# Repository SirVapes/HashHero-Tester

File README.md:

# HashHero
 Open Source Antminer Hashboard Tester

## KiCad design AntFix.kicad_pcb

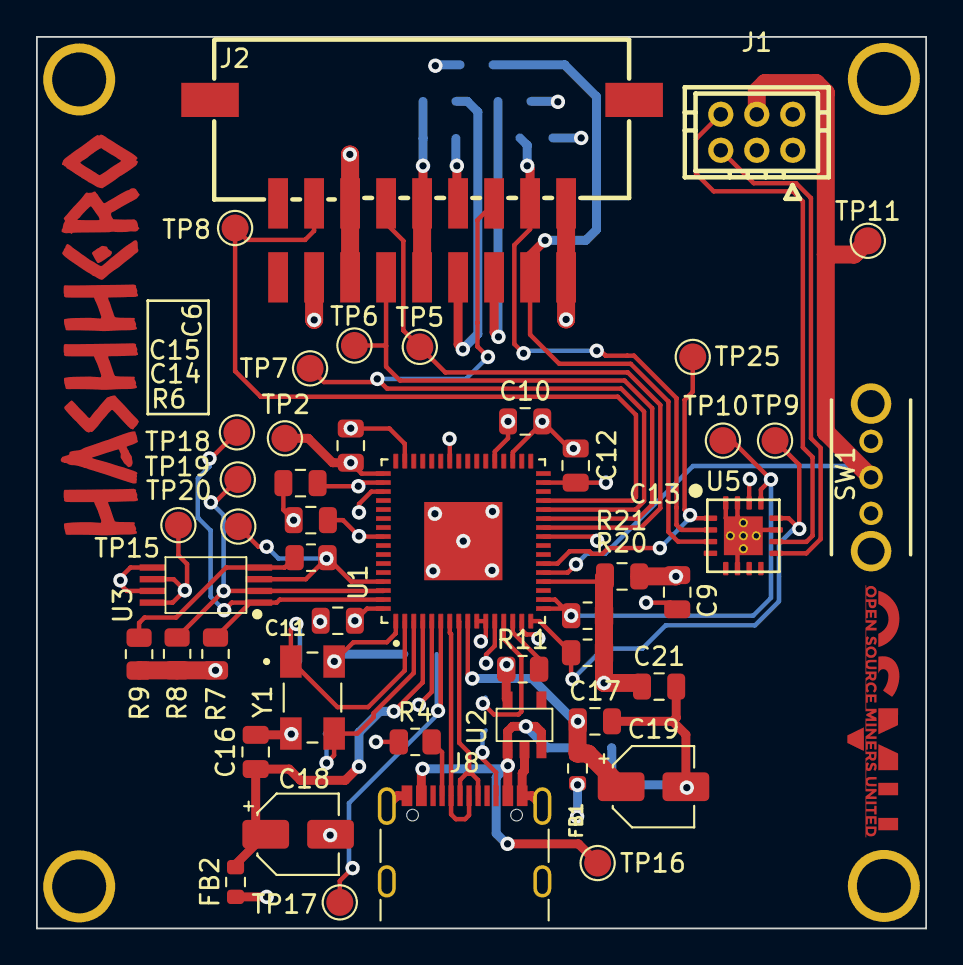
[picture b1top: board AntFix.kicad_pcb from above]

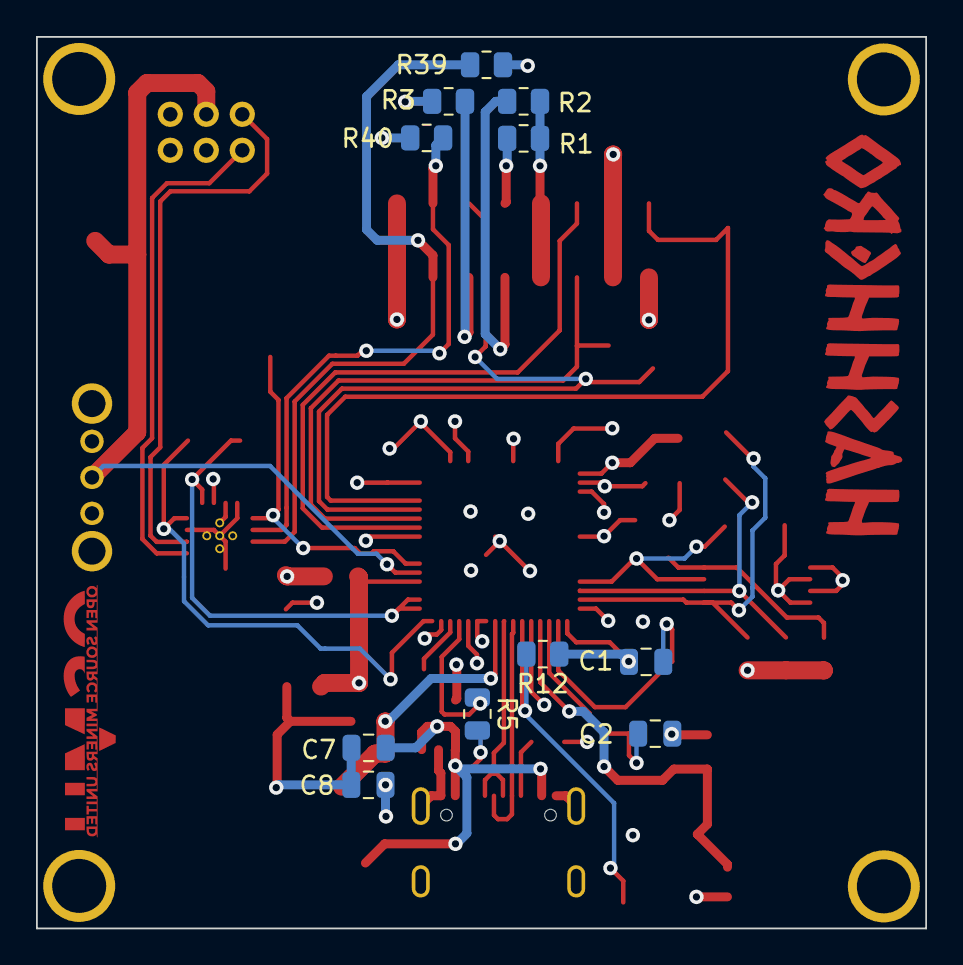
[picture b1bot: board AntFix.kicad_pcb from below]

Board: 4 copper layers, 49.4 x 49.5 mm, 62 parts (11 on the bottom side), 33 nets.

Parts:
C1, C2: 27pf; C_0805_2012Metric
C6: 3.3uF; C_0805_2012Metric
C7, C8: 1uF; C_0805_2012Metric
C9, C10, C11, C12, C13, C14, C15, C16, C17, C21: 0.1uF; C_0805_2012Metric
C18, C19: 4.7uF; CP_Elec_4x5.4
FB1, FB2: FerriteBead_Small; R_0603_1608Metric
H1, H2, H3, H4: MountingHole_Pad; MountingHole_3mm_Pad
J1: PSU Comm; CONN-TH_6P-P2.00_PHD-2X3A
J2: Hashboard0; CONN-SMD_X2026WRS-2X09D-LPSW
J8: USB_C_Receptacle_USB2.0; USB_C_Receptacle_GCT_USB4105-xx-A_16P_TopMnt_Horizontal
R1, R2, R3, R20, R21, R39, R40: 4.7K; R_0805_2012Metric
R4, R5: 5.1K; R_0805_2012Metric
R6: 2.2K; R_0805_2012Metric
R7, R8, R9: 10K; R_0805_2012Metric
R11: 1K; R_0805_2012Metric
R12: 12K; R_0805_2012Metric
SW1: SW_SPDT; OS102011MA1QN1
TP2, TP5, TP6, TP7, TP8, TP9, TP10, TP11, TP15, TP16, TP17, TP18, TP19, TP20, TP25: TestPoint; TestPoint_Pad_D1.5mm
U1: FT4232HQ; QFN50P900X900X105-65N
U2: RT9080-33GJ5
U3: M93C46-WDW6TP; TSSOP8_STM
U5: PCA9546ARGVR; QFN-16_EP_4x4_Pitch0.65mm
Y1: 12MHz; XTAL_405C35B12M00000

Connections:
/5V: C7.1, J8.A4 (VBUS), J8.A9 (VBUS), J8.B4 (VBUS), J8.B9 (VBUS), TP16.1, U2.1 (VIN), U2.3 (EN)
/A00: J2.8, R2.1
/A10: J2.7, R1.2
/A20: J2.6, R3.1
/PLUG0: J2.5, TP7.1, U1.28 (BDBUS2)
/PSU_EN: J1.5, SW1.2 (B), TP11.1, U1.21 (ADBUS4)
/RESET: TP25.1, U1.22 (ADBUS5), U5.1 (*RESET)
/RST0: J2.15, TP8.1, U1.29 (BDBUS3)
/RXD0: J2.12, TP6.1, U1.27 (BDBUS1)
/SCL: R20.1, TP9.1, U1.16 (ADBUS0), U5.12 (SCL)
/SCL0: J2.4, R39.1, U5.3 (SC0)
/SCL3: J1.6, U5.10 (SC3)
/SDA: R21.1, TP10.1, U1.17 (ADBUS1), U1.18 (ADBUS2), U5.13 (SDA)
/SDA0: J2.3, R40.1, U5.2 (SD0)
/SDA3: J1.3, U5.9 (SD3)
/TXD0: J2.11, TP5.1, U1.26 (BDBUS0)
/VPHY: C16.1, C18.1, FB2.2, U1.4 (VPHY)
/VPLL: C17.1, C19.1, FB1.2, U1.9 (VPLL)
GND: C1.2, C2.2, C6.2, C7.2, C8.2, C9.2, C10.2, C11.2, C12.2, C13.2, C14.2, C15.2, C16.2, C17.2, C18.2, C19.2, C21.2, H1.1, H2.1, H3.1, H4.1, J1.2, J2.1, J2.2, J2.9, J2.10, J2.13, J2.14, J8.A1 (GND), J8.A12 (GND), J8.B1 (GND), J8.B12 (GND), J8.S1 (SHIELD), R1.1, R2.2, R3.2, R4.1, R5.1, R12.1, SW1.1 (A), U1.1 (GND), U1.5 (GND), U1.10 (AGND), U1.11 (GND), U1.13 (TEST), U1.15 (GND), U1.25 (GND), U1.35 (GND), U1.47 (GND), U1.51 (GND), U1.65 (EPAD), U2.2 (GND), U3.5 (VSS), U3.7 (DU), U5.6 (GND), U5.11 (A2), U5.15 (A0), U5.16 (A1), U5.17 (EPAD), Y1.2 (GND), Y1.4 (GND__1)
unnamed: J8.A5 (CC1), R4.2
unnamed: J8.B5 (CC2), R5.2
unnamed: J8.A7 (D-), J8.B7 (D-), U1.7 (DM)
unnamed: J8.A6 (D+), J8.B6 (D+), U1.8 (DP)
unnamed: R8.1, TP19.1, U1.62 (EECLK), U3.2 (CLK)
unnamed: R7.1, TP18.1, U1.63 (EECS), U3.1 (CS)
unnamed: R6.1, TP20.1, U1.61 (EEDATA), U3.3 (D)
unnamed: C1.1, U1.2 (OSCI), Y1.1
unnamed: C2.1, U1.3 (OSCO), Y1.3
unnamed: R12.2, TP17.1, U1.6 (REF)
unnamed: R11.2, U1.14 (RESET#)
unnamed: R6.2, R9.1, U3.4 (Q)
VCCIO: C8.1, C12.1, C13.1, C14.1, C15.1, C21.1, FB1.1, FB2.1, J2.16, R7.2, R8.2, R9.2, R11.1, R20.2, R21.2, R39.2, R40.2, TP15.1, U1.20 (VCCIO), U1.31 (VCCIO), U1.42 (VCCIO), U1.50 (VREGIN), U1.56 (VCCIO), U2.5 (VOUT), U3.6 (ORG), U3.8 (VCC), U5.14 (VCC)
VCORE: C6.1, C9.1, C10.1, C11.1, TP2.1, U1.12 (VCORE), U1.37 (VCORE), U1.49 (VREGOUT), U1.64 (VCORE)

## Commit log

2024-01-05 Initial Upload
    Initial Upload
